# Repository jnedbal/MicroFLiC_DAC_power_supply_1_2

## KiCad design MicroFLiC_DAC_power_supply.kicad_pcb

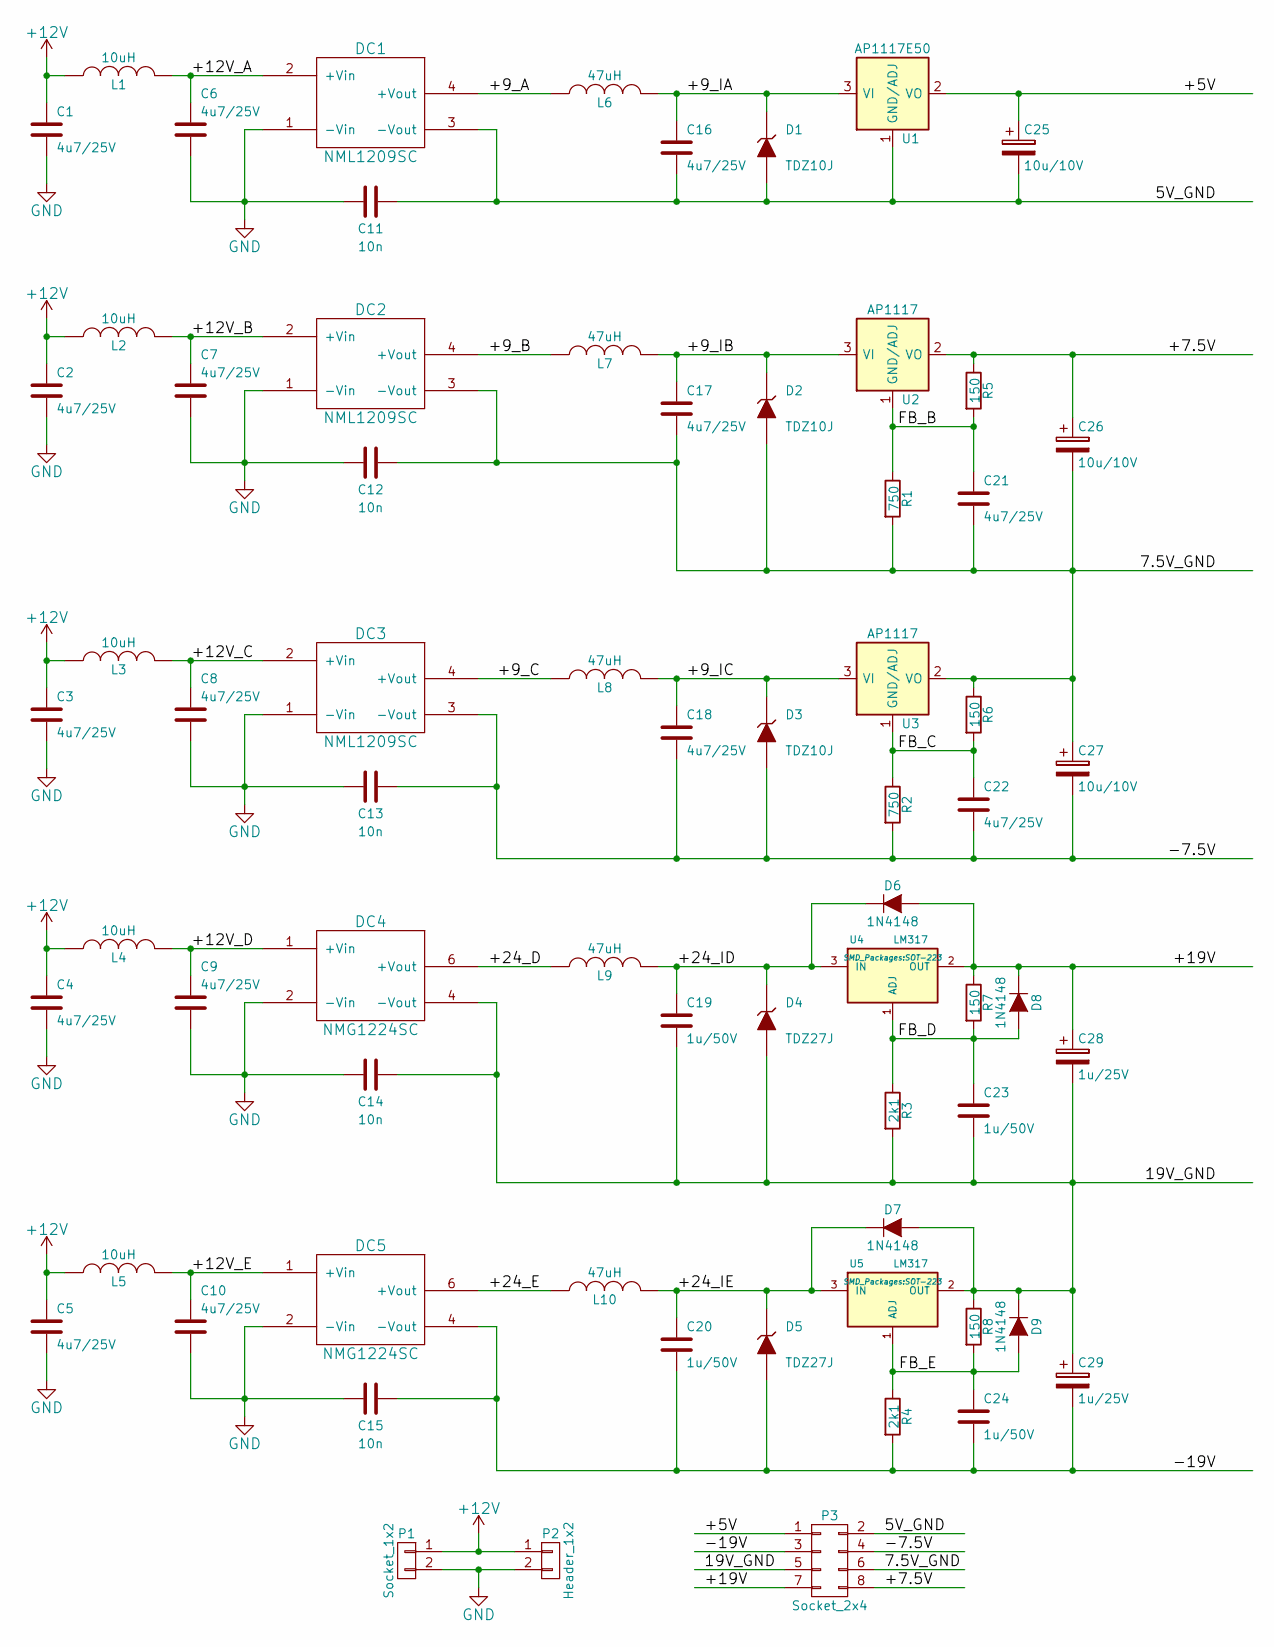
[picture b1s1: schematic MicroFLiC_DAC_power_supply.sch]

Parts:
C1, C2, C3, C4, C5, C6, C7, C8, C9, C10, C16, C17, C18, C21, C22: 4u7/25V; C_0805; Part Number GRM21BR61E475MA12L
C11, C12, C13, C14, C15: 10n; C_0805; Part Number MCU0805R103KCT
C19, C20, C23, C24: 1u/50V; C_0805; Part Number GRM219R61H105KA73D
C25, C26, C27: 10u/10V; TantalC_SizeA_EIA-3216_Reflow; Part Number TAJA106K010RNJ
C28, C29: 1u/25V; TantalC_SizeA_EIA-3216_Reflow; Part Number TRJA105K025RRJ
D1, D2, D3: TDZ10J; SOD-323_Zener; Part Number TDZ10J
D4, D5: TDZ27J; SOD-323_Zener; Part Number TDZ27J
D6, D7, D8, D9: 1N4148; SOD-323; Part Number 1N4148WS
DC1, DC2, DC3: NML1209SC; MurataNML; Part Number NML1209SC
DC4, DC5: NMG1224SC; MurataNMG; Part Number NMG1224SC
L1, L2, L3, L4, L5: 10uH; murata8200coil; Part Number 7440329100
L6, L7, L8, L9, L10: 47uH; murata8200coil; Part Number 82473C
P1: Socket_1x2; ESQ-102-33-G-S; Part Number ESQ-102-33-G-S
P2: Header_1x2; Pin_Header_Straight_1x02; Part Number M20-9990245
P3: Socket_2x4; ESQ-104-33-G-D; Part Number ESQ-104-33-G-D
R1, R2: 750; R_0805; Part Number MCMR08X7500FTL
R3, R4: 2k1; R_0805; Part Number CRCW08052K10FKEA
R5, R6, R7, R8: 150; R_0805; Part Number MCWR08X1500FTL
U1: AP1117E50; SOT-223; Part Number AP1117E50G-13
U2, U3: AP1117; SOT-223; Part Number AP1117EG-13
U4, U5: LM317; SOT-223; Part Number LM317DCY

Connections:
+12V: C1.1, C2.1, C3.1, C4.1, C5.1, L1.1, L2.1, L3.1, L4.1, L5.1, P1.1, P2.1
/5V_GND: C11.1, C16.2, C25.2, D1.2 (A), DC1.3 (-Vout), P3.2, U1.1 (GND/ADJ)
/7.5V_GND: C12.1, C17.2, C21.2, C26.2, C27.1, D2.2 (A), DC2.3 (-Vout), P3.6, R1.2, R6.1, U3.2 (VO)
/19V_GND: C14.1, C19.2, C23.2, C28.2, C29.1, D4.2 (A), D7.2 (A), D9.1 (K), DC4.4 (-Vout), P3.5, R3.2, R8.1, U5.2 (OUT)
/+5V: C25.1, P3.1, U1.2 (VO)
/+7.5V: C26.1, P3.8, R5.1, U2.2 (VO)
/+9_A: DC1.4 (+Vout), L6.1
/+9_B: DC2.4 (+Vout), L7.1
/+9_C: DC3.4 (+Vout), L8.1
/+9_IA: C16.1, D1.1 (K), L6.2, U1.3 (VI)
/+9_IB: C17.1, D2.1 (K), L7.2, U2.3 (VI)
/+9_IC: C18.1, D3.1 (K), L8.2, U3.3 (VI)
/+12V_A: C6.1, DC1.2 (+Vin), L1.2
/+12V_B: C7.1, DC2.2 (+Vin), L2.2
/+12V_C: C8.1, DC3.2 (+Vin), L3.2
/+12V_D: C9.1, DC4.1 (+Vin), L4.2
/+12V_E: C10.1, DC5.1 (+Vin), L5.2
/+19V: C28.1, D6.2 (A), D8.1 (K), P3.7, R7.1, U4.2 (OUT)
/+24_D: DC4.6 (+Vout), L9.1
/+24_E: DC5.6 (+Vout), L10.1
/+24_ID: C19.1, D4.1 (K), D6.1 (K), L9.2, U4.3 (IN)
/+24_IE: C20.1, D5.1 (K), D7.1 (K), L10.2, U5.3 (IN)
/-7.5V: C13.1, C18.2, C22.2, C27.2, D3.2 (A), DC3.3 (-Vout), P3.4, R2.2
/-19V: C15.1, C20.2, C24.2, C29.2, D5.2 (A), DC5.4 (-Vout), P3.3, R4.2
/FB_B: C21.1, R1.1, R5.2, U2.1 (GND/ADJ)
/FB_C: C22.1, R2.1, R6.2, U3.1 (GND/ADJ)
/FB_D: C23.1, D8.2 (A), R3.1, R7.2, U4.1 (ADJ)
/FB_E: C24.1, D9.2 (A), R4.1, R8.2, U5.1 (ADJ)
GND: C1.2, C2.2, C3.2, C4.2, C5.2, C6.2, C7.2, C8.2, C9.2, C10.2, C11.2, C12.2, C13.2, C14.2, C15.2, DC1.1 (-Vin), DC2.1 (-Vin), DC3.1 (-Vin), DC4.2 (-Vin), DC5.2 (-Vin), P1.2, P2.2

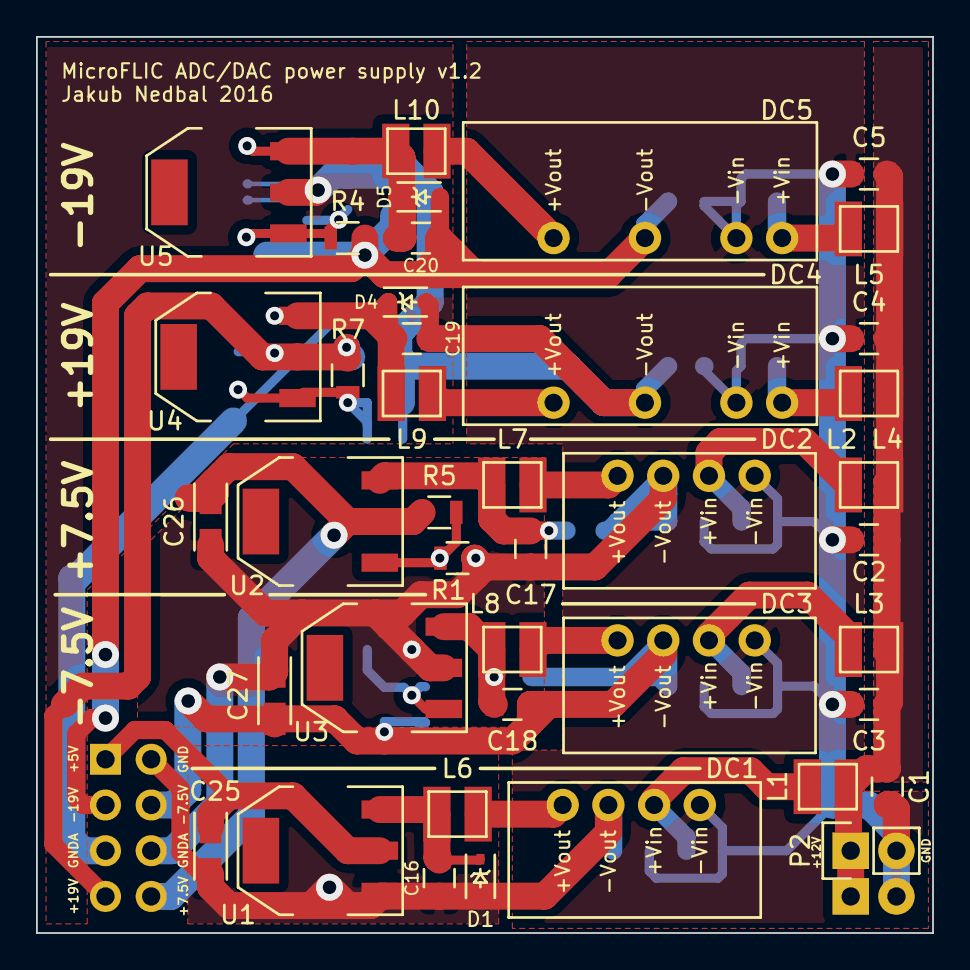
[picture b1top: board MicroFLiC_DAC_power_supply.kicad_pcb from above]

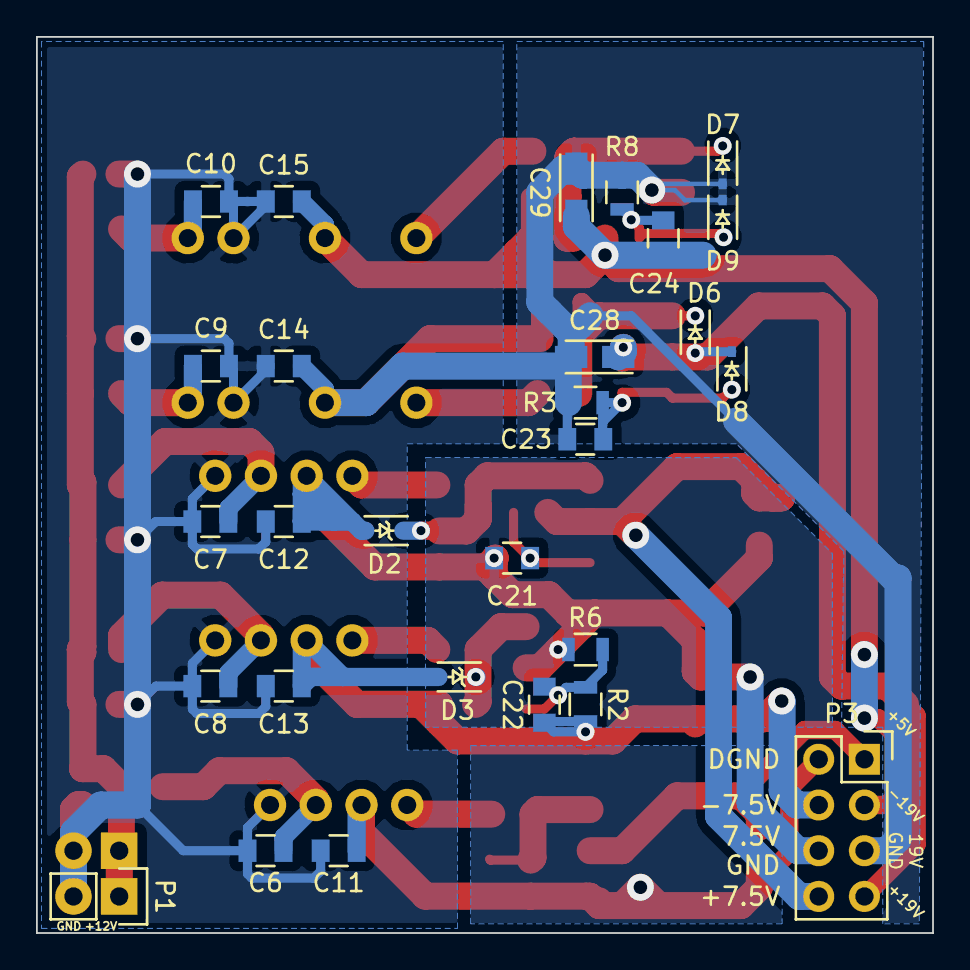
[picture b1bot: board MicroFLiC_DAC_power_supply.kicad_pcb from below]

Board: 2 copper layers, 49.8 x 49.8 mm, 69 parts (28 on the bottom side), 29 nets.

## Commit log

2016-02-02 Version 1.1 with fixed DC-DC controller pinout and extra filtering capacitors.
2016-02-02 Completed part descriptions
2016-02-03 Added feedback filtering capacitors and protection diodes
2016-02-03 Created output files
2016-02-03 Added drl file
2016-02-03 Created .gitignore file to ignore the ZIP file
2016-02-11 Fixed capacitor order code
2016-02-11 Updated part descriptions
2016-02-14 Removed trailing version number
2016-02-14 Fixed capacitor and DC-DC converter descriptiions
2016-02-17 Fixed LDO feedback resistors and capacitors
2016-02-18 Fixed power output connector orientation
2016-02-19 Production files for Seeedstudio
2016-02-26 Fixed connector descriptions
2016-03-18 Changed SOD-323 packages for larger pads.
